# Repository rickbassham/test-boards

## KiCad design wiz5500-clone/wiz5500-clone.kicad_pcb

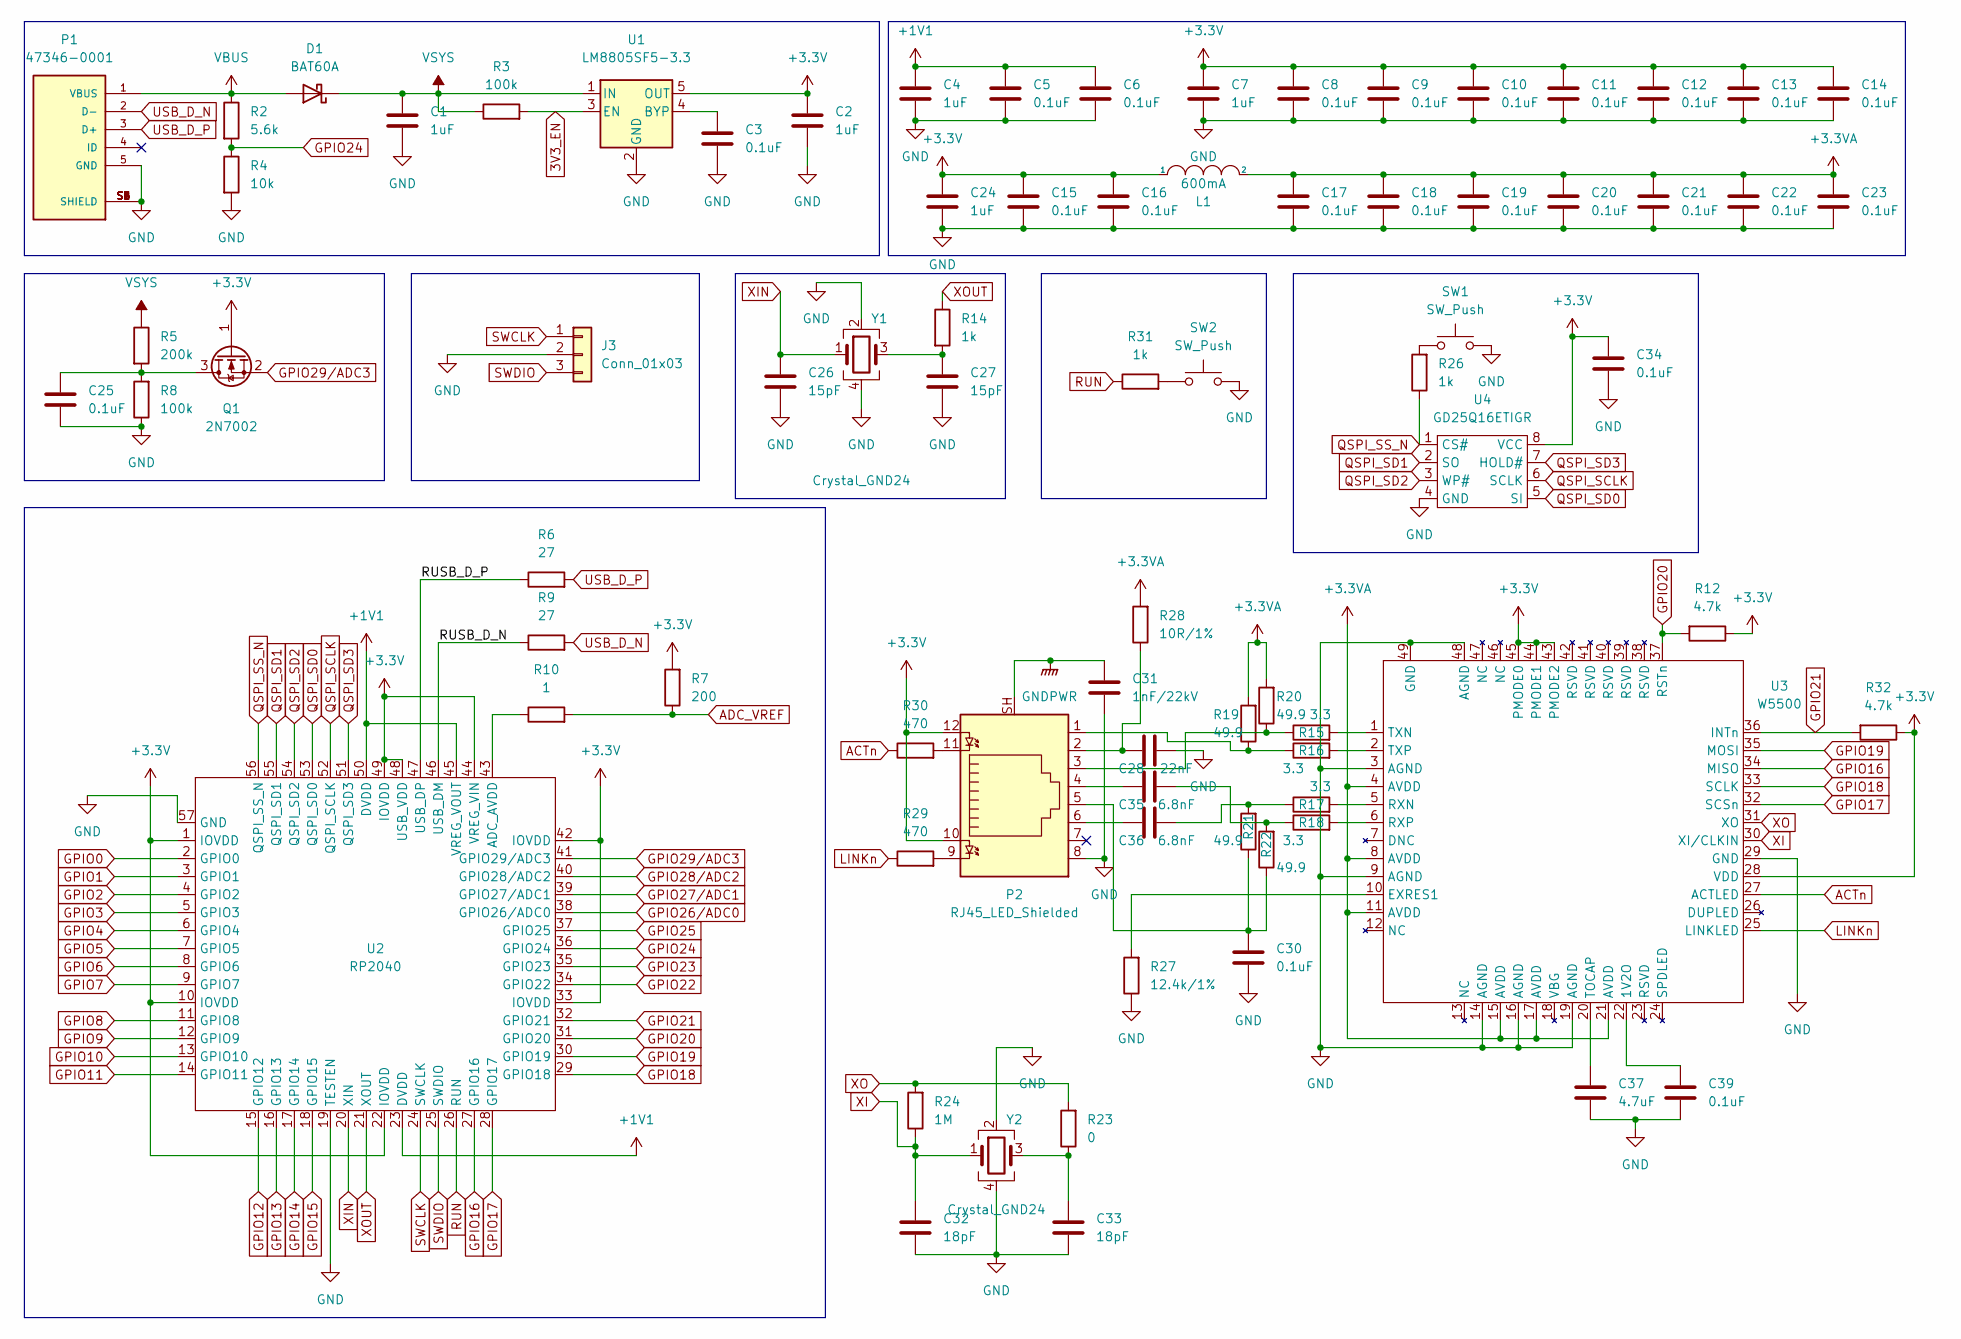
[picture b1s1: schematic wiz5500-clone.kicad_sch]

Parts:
C1, C2, C4, C7, C24: 1uF; C_0201_0603Metric
C3, C5, C6, C8, C9, C10, C11, C12, C13, C14, C15, C16, C17, C18, C19, C20, C21, C22, C23, C25, C30, C34, C39: 0.1uF; C_0201_0603Metric
C26, C27: 15pF; C_0201_0603Metric
C28: 22nF; C_0201_0603Metric
C31: 1nF/22kV; C_0201_0603Metric
C32, C33: 18pF; C_0201_0603Metric
C35, C36: 6.8nF; C_0201_0603Metric
C37: 4.7uF; C_0201_0603Metric
D1: BAT60A; D_SOD-323; Manufacturer PN BAT60AE6327HTSA1; lcsc C117485
J3: Conn_01x03; PinHeader_1x03_P2.54mm_Vertical
L1: 600mA; L_0603_1608Metric; lcsc C280478
P1: 47346-0001; MOLEX_47346-0001; lcsc C132560
P2: RJ45_LED_Shielded; J1B1211CCD; Manufacturer PN J1B1211CCD; lcsc C910371
Q1: 2N7002; SOT-23
R2: 5.6k; R_0201_0603Metric
R3, R8: 100k; R_0201_0603Metric
R4: 10k; R_0201_0603Metric
R5: 200k; R_0201_0603Metric
R6, R9: 27; R_0201_0603Metric
R7: 200; R_0201_0603Metric
R10: 1; R_0201_0603Metric
R12, R32: 4.7k; R_0201_0603Metric
R14, R26, R31: 1k; R_0201_0603Metric
R15, R16, R17, R18: 3.3; R_0201_0603Metric
R19, R20, R21, R22: 49.9; R_0201_0603Metric
R23: 0; R_0201_0603Metric
R24: 1M; R_0201_0603Metric
R27: 12.4k/1%; R_0201_0603Metric
R28: 10R/1%; R_0201_0603Metric
R29, R30: 470; R_0201_0603Metric
SW1, SW2: SW_Push; SW_TS-1187A-B-A-B; lcsc C318884
U1: LM8805SF5-3.3; SOT-23-5; lcsc C126077
U2: RP2040; QFN-56-1EP_7x7mm_P0.4mm_EP5.6x5.6mm
U3: W5500; LQFP-48-1EP_7x7mm_P0.5mm_EP3.6x3.6mm
U4: GD25Q16ETIGR; SOP-8_3.9x4.9mm_P1.27mm
Y1: Crystal_GND24; Crystal_SMD_3225-4Pin_3.2x2.5mm; lcsc C133334
Y2: Crystal_GND24; Crystal_SMD_3225-4Pin_3.2x2.5mm; lcsc C700768

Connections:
3V3_EN: R3.2, U1.3 (EN)
+1V1: C4.1, C5.1, C6.1, U2.23 (DVDD), U2.45 (VREG_VOUT), U2.50 (DVDD)
+3.3VA: C17.1, C18.1, C19.1, C20.1, C21.1, C22.1, C23.1, L1.2, R19.2, R20.2, R28.2, U3.4 (AVDD), U3.8 (AVDD), U3.11 (AVDD), U3.15 (AVDD), U3.17 (AVDD), U3.21 (AVDD)
+3V3: C2.1, C7.1, C8.1, C9.1, C10.1, C11.1, C12.1, C13.1, C14.1, C15.1, C16.1, C24.1, C34.1, L1.1, P2.10, P2.12, Q1.1 (G), R7.2, R12.1, R32.1, U1.5 (OUT), U2.1 (IOVDD), U2.10 (IOVDD), U2.22 (IOVDD), U2.33 (IOVDD), U2.42 (IOVDD), U2.44 (VREG_VIN), U2.48 (USB_VDD), U2.49 (IOVDD), U3.28 (VDD), U3.43 (PMODE2), U3.44 (PMODE1), U3.45 (PMODE0), U4.8 (VCC)
/RUSB_D_N: R9.1, U2.46 (USB_DM)
/RUSB_D_P: R6.1, U2.47 (USB_DP)
ACTn: R30.1, U3.27 (ACTLED)
ADC_VREF: R7.1, R10.2
GND: C1.2, C2.2, C3.2, C4.2, C5.2, C6.2, C7.2, C8.2, C9.2, C10.2, C11.2, C12.2, C13.2, C14.2, C15.2, C16.2, C17.2, C18.2, C19.2, C20.2, C21.2, C22.2, C23.2, C24.2, C25.2, C26.2, C27.2, C28.2, C30.2, C31.2, C32.2, C33.2, C34.2, C37.2, C39.2, J3.2, P1.5 (GND), P1.S1 (SHIELD), P1.S2 (SHIELD), P1.S3 (SHIELD), P1.S4 (SHIELD), P1.S5 (SHIELD), P1.S6 (SHIELD), P2.8, R4.2, R8.1, R27.1, SW1.2, SW2.2, U1.2 (GND), U2.19 (TESTEN), U2.57 (GND), U3.3 (AGND), U3.9 (AGND), U3.14 (AGND), U3.16 (AGND), U3.19 (AGND), U3.29 (GND), U3.48 (AGND), U3.49 (GND), U4.4 (GND), Y1.2, Y1.4, Y2.2, Y2.4
GNDPWR: C31.1, P2.SH
GPIO0: U2.2 (GPIO0)
GPIO1: U2.3 (GPIO1)
GPIO2: U2.4 (GPIO2)
GPIO3: U2.5 (GPIO3)
GPIO4: U2.6 (GPIO4)
GPIO5: U2.7 (GPIO5)
GPIO6: U2.8 (GPIO6)
GPIO7: U2.9 (GPIO7)
GPIO8: U2.11 (GPIO8)
GPIO9: U2.12 (GPIO9)
GPIO10: U2.13 (GPIO10)
GPIO11: U2.14 (GPIO11)
GPIO12: U2.15 (GPIO12)
GPIO13: U2.16 (GPIO13)
GPIO14: U2.17 (GPIO14)
GPIO15: U2.18 (GPIO15)
GPIO16: U2.27 (GPIO16), U3.34 (MISO)
GPIO17: U2.28 (GPIO17), U3.32 (SCSn)
GPIO18: U2.29 (GPIO18), U3.33 (SCLK)
GPIO19: U2.30 (GPIO19), U3.35 (MOSI)
GPIO20: R12.2, U2.31 (GPIO20), U3.37 (RSTn)
GPIO21: R32.2, U2.32 (GPIO21), U3.36 (INTn)
GPIO22: U2.34 (GPIO22)
GPIO23: U2.35 (GPIO23)
GPIO24: R2.2, R4.1, U2.36 (GPIO24)
GPIO25: U2.37 (GPIO25)
GPIO26/ADC0: U2.38 (GPIO26/ADC0)
GPIO27/ADC1: U2.39 (GPIO27/ADC1)
GPIO28/ADC2: U2.40 (GPIO28/ADC2)
GPIO29/ADC3: Q1.2 (S), U2.41 (GPIO29/ADC3)
LINKn: R29.1, U3.25 (LINKLED)
unnamed: C3.1, U1.4 (BYP)
unnamed: C25.1, Q1.3 (D), R5.2, R8.2
unnamed: C27.1, R14.2, Y1.3
unnamed: C28.1, P2.2, R28.1
unnamed: C30.1, P2.5, R21.1, R22.1
unnamed: C33.1, R23.1, Y2.3
unnamed: C35.1, P2.4
unnamed: C35.2, R18.1, R22.2
unnamed: C36.1, P2.6
unnamed: C36.2, R17.1, R21.2
unnamed: C37.1, U3.20 (TOCAP)
unnamed: C39.1, U3.22 (1V2O)
unnamed: P2.1, R16.1, R19.1
unnamed: P2.3, R15.1, R20.1
unnamed: P2.9, R29.2
unnamed: P2.11, R30.2
unnamed: R10.1, U2.43 (ADC_AVDD)
unnamed: R15.2, U3.1 (TXN)
unnamed: R16.2, U3.2 (TXP)
unnamed: R17.2, U3.5 (RXN)
unnamed: R18.2, U3.6 (RXP)
unnamed: R26.2, SW1.1
unnamed: R27.2, U3.10 (EXRES1)
unnamed: R31.2, SW2.1
QSPI_SCLK: U2.52 (QSPI_SCLK), U4.6 (SCLK)
QSPI_SD0: U2.53 (QSPI_SD0), U4.5 (SI)
QSPI_SD1: U2.55 (QSPI_SD1), U4.2 (SO)
QSPI_SD2: U2.54 (QSPI_SD2), U4.3 (WP#)
QSPI_SD3: U2.51 (QSPI_SD3), U4.7 (HOLD#)
QSPI_SS_N: R26.1, U2.56 (QSPI_SS_N), U4.1 (CS#)
RUN: R31.1, U2.26 (RUN)
SWCLK: J3.1, U2.24 (SWCLK)
SWDIO: J3.3, U2.25 (SWDIO)
USB_D_N: P1.2 (D-), R9.2
USB_D_P: P1.3 (D+), R6.2
VBUS: D1.2 (A), P1.1 (VBUS), R2.1
VSYS: C1.1, D1.1 (K), R3.1, R5.1, U1.1 (IN)
XI: C32.1, R24.1, U3.30 (XI/CLKIN), Y2.1
XIN: C26.1, U2.20 (XIN), Y1.1
XO: R23.2, R24.2, U3.31 (XO)
XOUT: R14.1, U2.21 (XOUT)

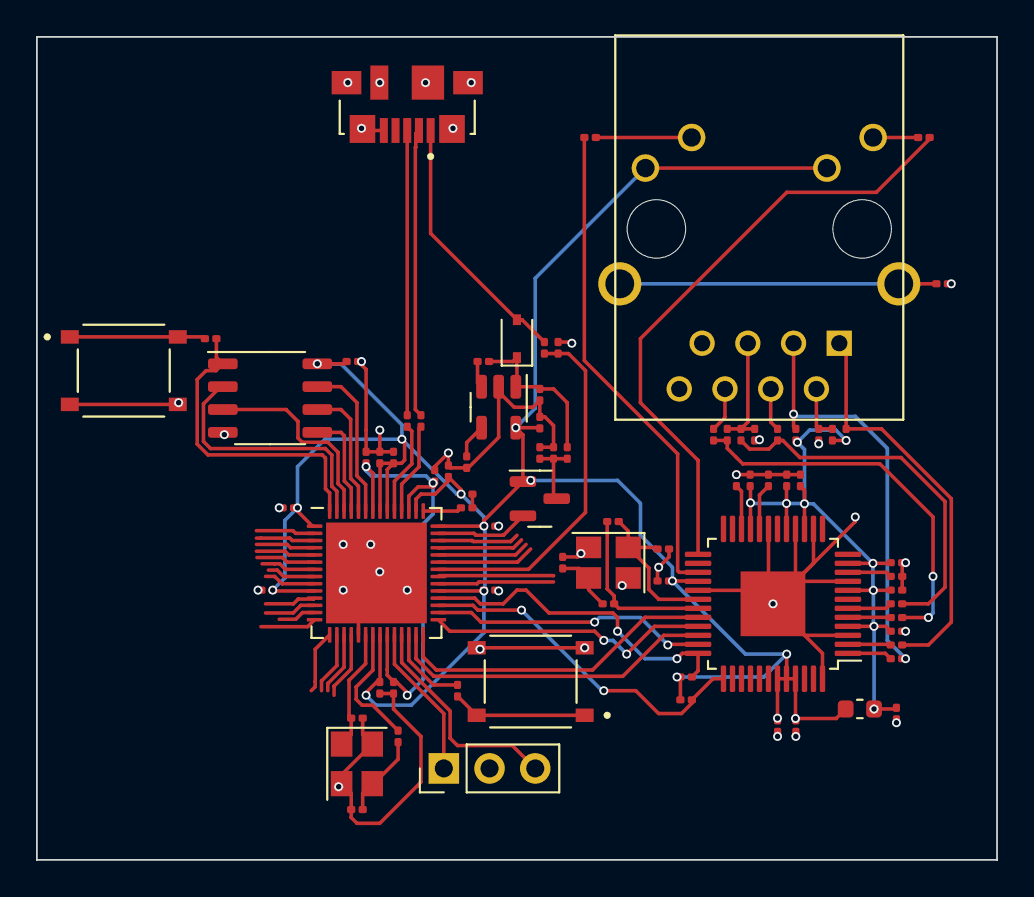
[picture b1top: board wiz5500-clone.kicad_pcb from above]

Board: 2 copper layers, 53.3 x 45.7 mm, 79 parts (0 on the bottom side), 60 nets.
